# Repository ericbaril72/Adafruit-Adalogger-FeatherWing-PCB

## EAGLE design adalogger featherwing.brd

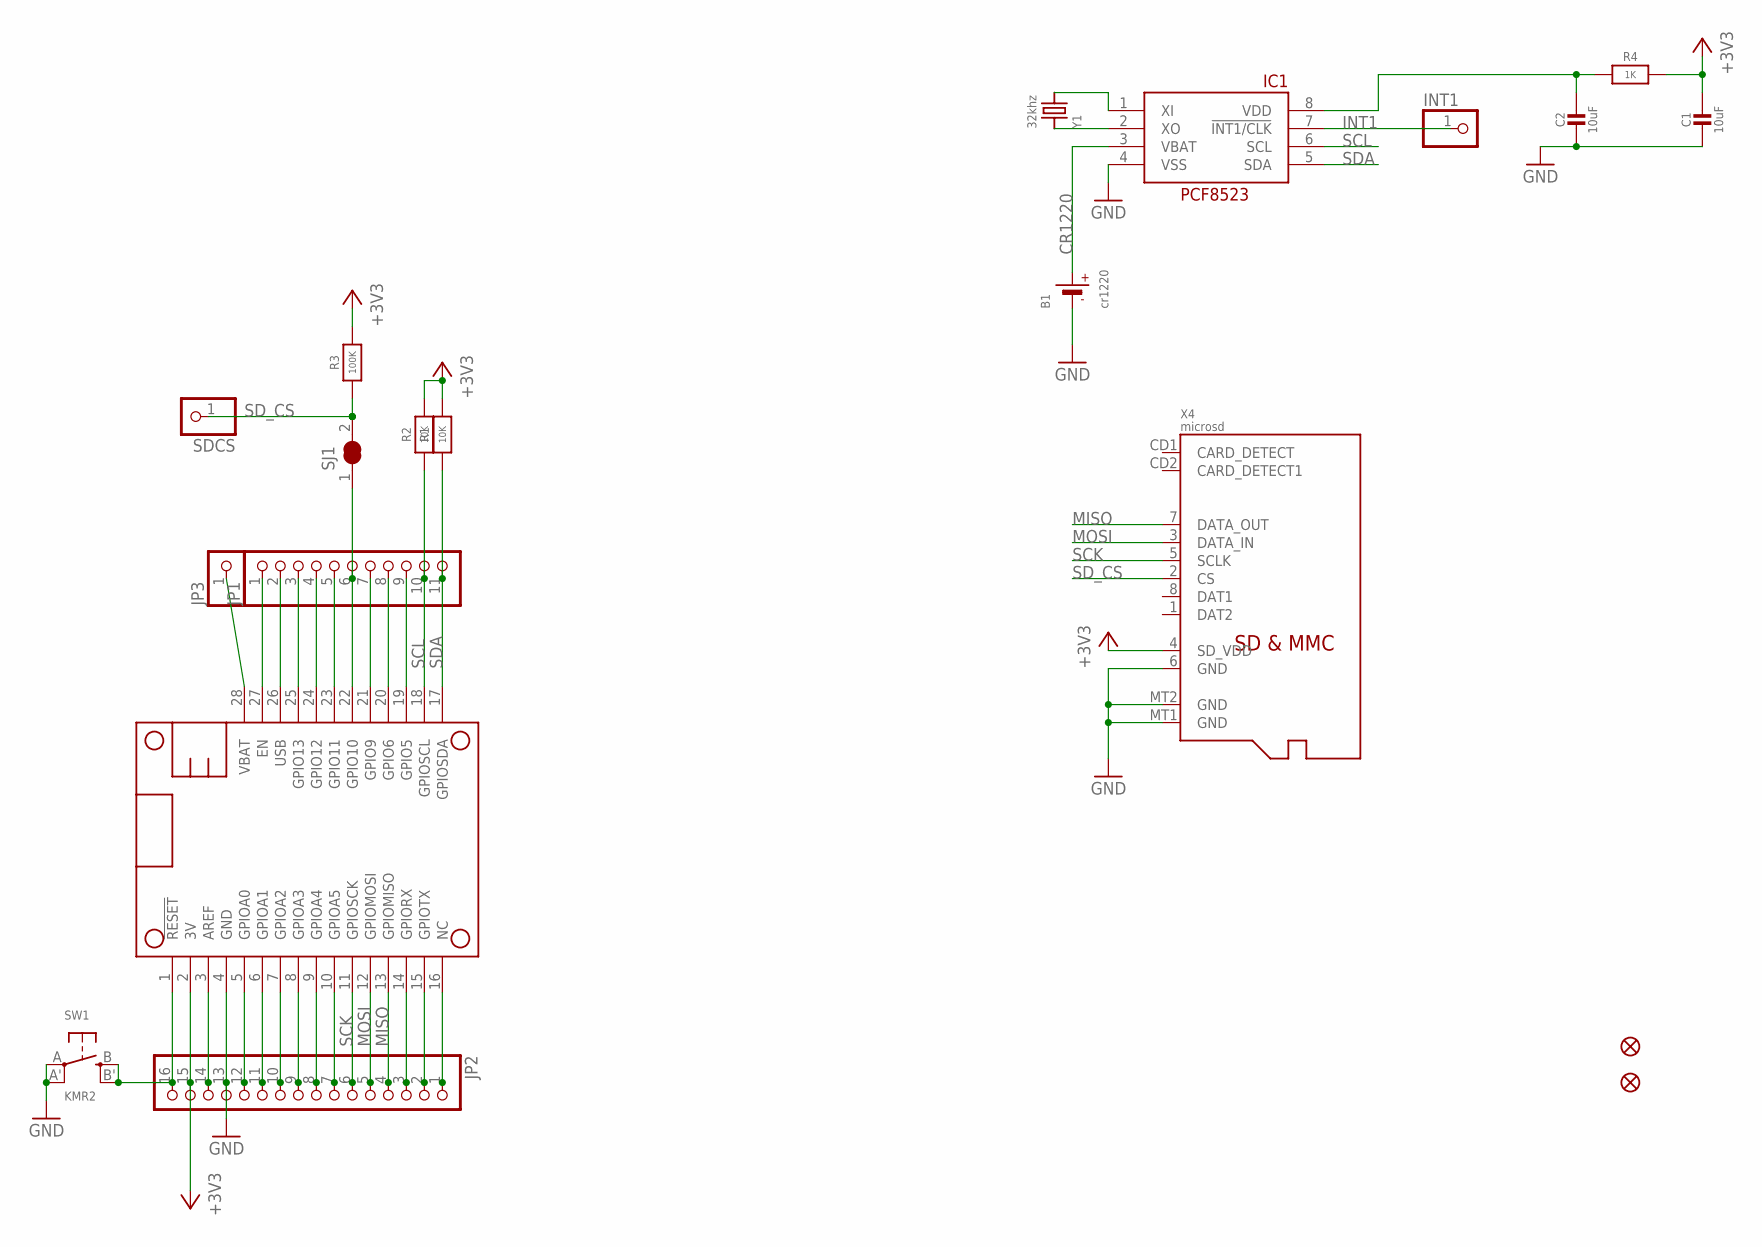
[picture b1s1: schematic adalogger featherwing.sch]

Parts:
B1: cr1220; CR1220-2
C1, C2: 10uF; 0805-NO
FID1, FID2: FIDUCIAL""; FIDUCIAL_1MM
IC1: RTC_PCF8523T; SOIC8_150MIL
INT1: HEADER-1X1ROUND; 1X01_ROUND
JP1: HEADER-1X11; 1X11_ROUND
JP2: HEADER-1X16ROUND; 1X16_ROUND
JP3: HEADER-1X1ROUND; 1X01_ROUND
MS1: FEATHERWING_NODIM; FEATHERWING_DIM
R1, R2: 10K; 0805-NO
R3: 100K; 0805-NO
R4: 1K; 0805-NO
SDCS: HEADER-1X1ROUND; 1X01_ROUND
SJ1: SOLDERJUMPER_CLOSED; SOLDERJUMPER_CLOSEDWIRE
SW1: KMR2; BTN_KMR2_4.6X2.8
X4: microsd; MICROSD
Y1: 32khz; CRYSTAL_8X3.8

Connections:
+3V3: C1.1, JP2.15, MS1.2 (3V), R1.2, R2.2, R3.2, R4.1, X4.4 (SD_VDD)
CR1220: B1.+, IC1.3 (VBAT)
D10: JP1.6, MS1.22 (GPIO10), SJ1.1
GND: B1.-, C1.2, C2.2, IC1.4 (VSS), JP2.13, MS1.4 (GND), SW1.A, SW1.A' (P1), X4.6 (GND), X4.MT1 (GND), X4.MT2 (GND)
INT1: IC1.7 (!INT1/CLK), INT1.1
MISO: JP2.4, MS1.13 (GPIOMISO), X4.7 (DATA_OUT)
MOSI: JP2.5, MS1.12 (GPIOMOSI), X4.3 (DATA_IN)
unnamed: JP2.16, MS1.1 (!RESET), SW1.B (S), SW1.B' (S1)
unnamed: JP2.1, MS1.16 (NC)
unnamed: JP1.3, MS1.25 (GPIO13)
unnamed: JP2.2, MS1.15 (GPIOTX)
unnamed: JP1.4, MS1.24 (GPIO12)
unnamed: JP2.3, MS1.14 (GPIORX)
unnamed: IC1.1 (XI), Y1.P$4 (2)
unnamed: IC1.2 (XO), Y1.P$1 (1)
unnamed: JP2.7, MS1.10 (GPIOA5)
unnamed: JP2.8, MS1.9 (GPIOA4)
unnamed: JP2.9, MS1.8 (GPIOA3)
unnamed: JP2.10, MS1.7 (GPIOA2)
unnamed: JP2.11, MS1.6 (GPIOA1)
unnamed: JP2.12, MS1.5 (GPIOA0)
unnamed: JP1.1, MS1.27 (EN)
unnamed: JP2.14, MS1.3 (AREF)
unnamed: JP1.5, MS1.23 (GPIO11)
unnamed: JP1.7, MS1.21 (GPIO9)
unnamed: JP1.8, MS1.20 (GPIO6)
unnamed: JP1.9, MS1.19 (GPIO5)
PCFVDD: C2.1, IC1.8 (VDD), R4.2
SCK: JP2.6, MS1.11 (GPIOSCK), X4.5 (SCLK)
SCL: IC1.6 (SCL), JP1.10, MS1.18 (GPIOSCL), R2.1
SDA: IC1.5 (SDA), JP1.11, MS1.17 (GPIOSDA), R1.1
SD_CS: R3.1, SDCS.1, SJ1.2, X4.2 (CS)
USB: JP1.2, MS1.26 (USB)
VBAT: JP3.1, MS1.28 (VBAT)

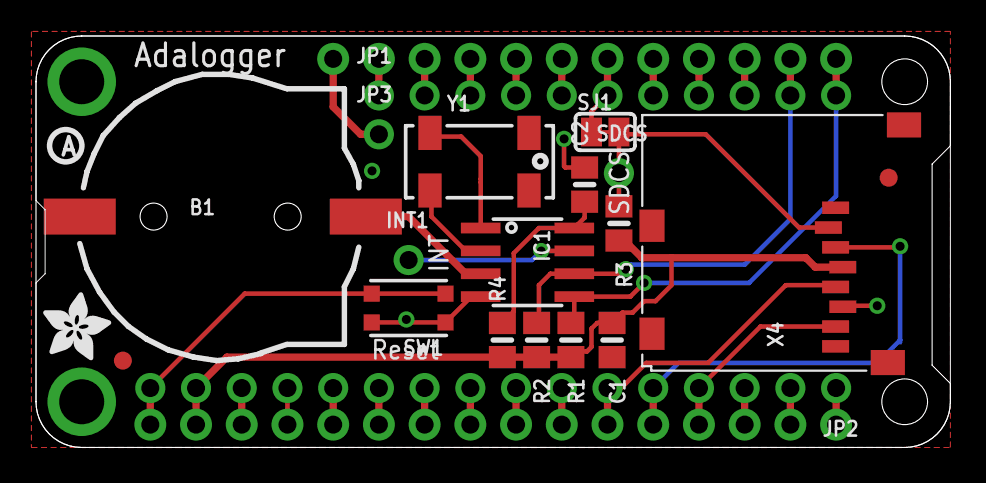
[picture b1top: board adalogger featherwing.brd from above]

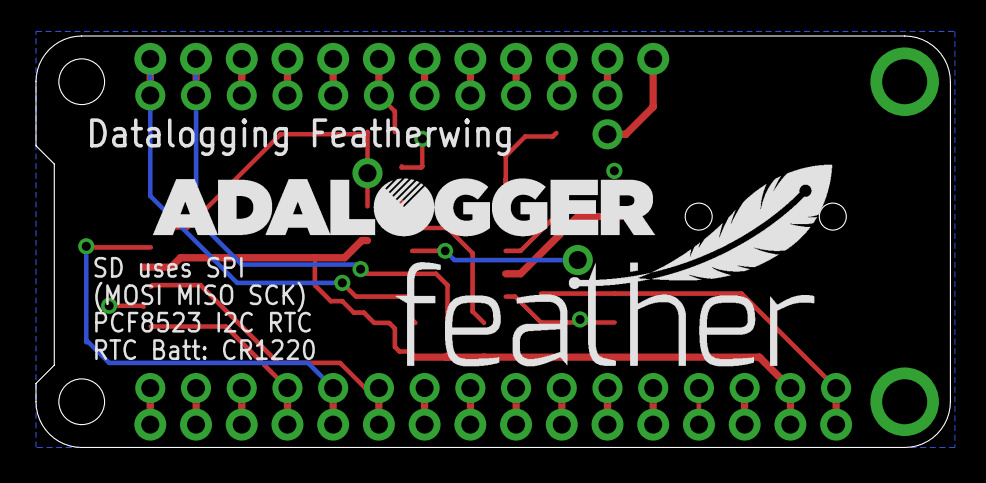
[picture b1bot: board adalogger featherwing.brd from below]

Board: 2 copper layers, 50.8 x 22.9 mm, 24 parts (2 on the bottom side), 34 nets.

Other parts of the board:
U$2: FEATHERLOGO
U$3: ADALOGGER_LOGO
U$4: ADAFRUIT_3.5MM
U$5: PCBFEAT-REV-040

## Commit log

2016-12-14 added RC network on PCF vdd line
